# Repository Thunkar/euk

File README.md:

# EUK Split Keyboard

A split ergonomic keyboard project with customizable accessories and per-key RGB lighting.

## Features

- Split design for ergonomic typing
- Hot-swappable MX switches
- Per-key RGB lighting (SK6812 mini-e LEDs)
- RP2040-based controller
- Optional accessories:
  - OLED screen
  - Rotary encoder
  - Analog joystick
  - Potentiometer
  - Tenting support

## Documentation

- [Bill of Materials (BOM)](./split/docs/BOM.md) - Complete list of components needed
- [Ordering PCBs](./split/docs/ORDERING_PCBS.md) - Guide for ordering the printed circuit boards
- [Assembly Guide](./split/docs/ASSEMBLY.md) - Step-by-step assembly instructions

## Project Structure

- `cad/` - 3D printable case and accessory files
- `pcb/` - KiCad PCB design files
- `docs/` - Documentation and guides
- `via.layout.json` - VIA keyboard configurator layout
- `via.definition.json` - VIA keyboard definition
- `kle.definition.json` - https://keyboard-layout-editor.com/ definition

## Getting Started

1. Review the [BOM](docs/BOM.md) to buy all required components
2. Follow the [PCB ordering guide](docs/ORDERING_PCBS.md) and get yourself some boards
3. Print the required parts from the `cad/` directory
4. Follow the [assembly guide](docs/ASSEMBLY.md) to build it!

## Firmware

This keyboard uses QMK/VIA firmware. Use the included `via.layout.json` file to configure your keyboard layout in [VIA](https://usevia.app/).

At the moment, use the QMK fork at https://github.com/Thunkar/qmk_firmware

After installation, flash with:

`qmk flash -kb euk/split -km default`

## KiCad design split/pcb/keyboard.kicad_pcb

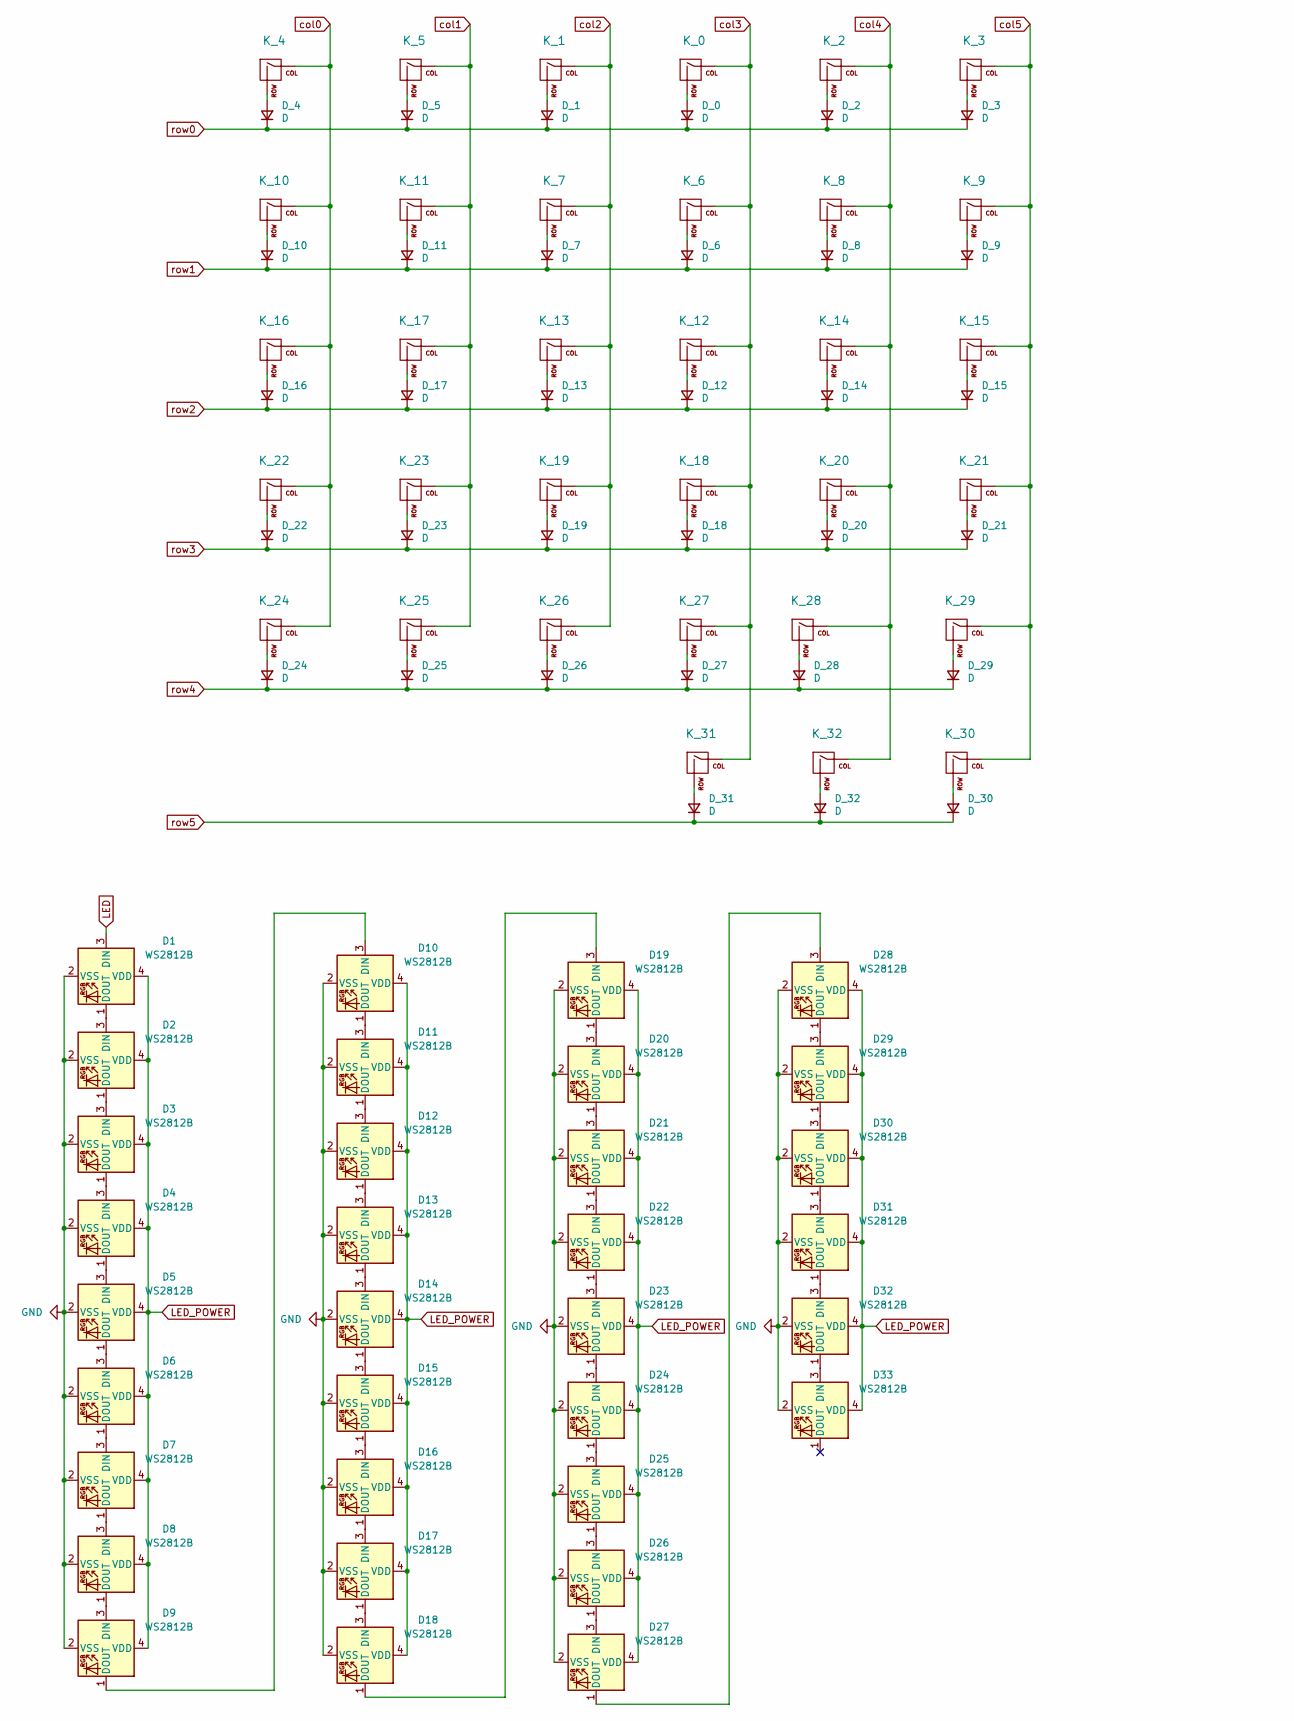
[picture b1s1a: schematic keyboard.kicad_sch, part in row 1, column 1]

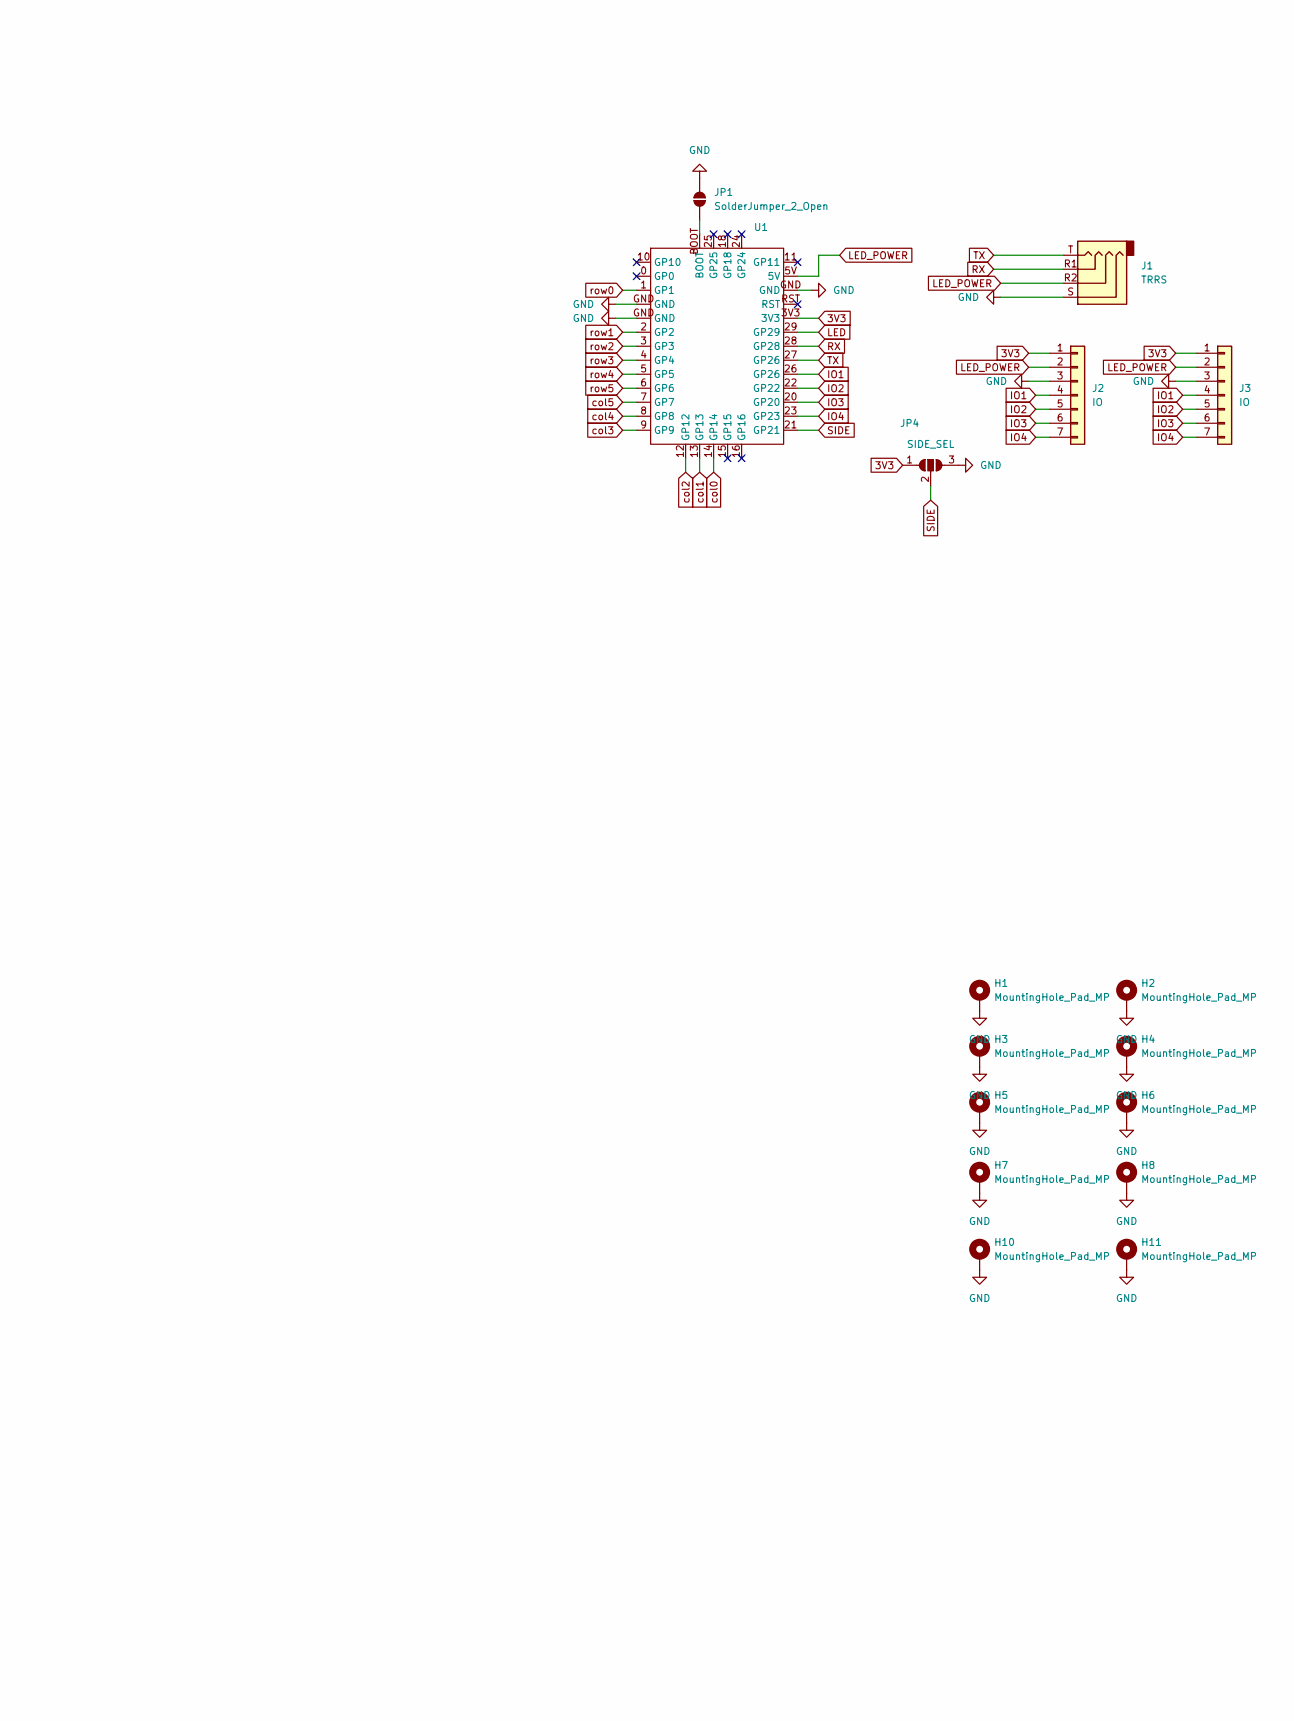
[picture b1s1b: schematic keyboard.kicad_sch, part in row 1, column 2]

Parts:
D1, D2, D3, D4, D5, D6, D7, D8, D9, D10, D11, D12, D13, D14, D15, D16, D17, D18, D19, D20, D21, D22, D23, D24, D25, D26, D27, D28, D29, D30, D31, D32, D33: WS2812B; SK6812-MINI-E
D_0, D_1, D_2, D_3, D_4, D_5, D_6, D_7, D_8, D_9, D_10, D_11, D_12, D_13, D_14, D_15, D_16, D_17, D_18, D_19, D_20, D_21, D_22, D_23, D_24, D_25, D_26, D_27, D_28, D_29, D_30, D_31, D_32: D; D_SOD-123_Reversible
H1, H2, H3, H4, H5, H6, H7, H8, H10, H11: MountingHole_Pad_MP; MountingHole_2.2mm_M2_DIN965_Pad
J1: TRRS; TRRS_JACK_MJ4PP9
J2, J3: IO; PinHeader_1x07_P2.54mm_Vertical
JP1: SolderJumper_2_Open; SolderJumper-2_P1.3mm_Open_Pad1.0x1.5mm
JP4: SIDE_SEL; SolderJumper-3_P1.3mm_Open_Pad1.0x1.5mm
K_0, K_1, K_2, K_3, K_4, K_5, K_6, K_7, K_8, K_9, K_10, K_11, K_12, K_13, K_14, K_15, K_16, K_17, K_18, K_19, K_20, K_21, K_22, K_23, K_24, K_25, K_26, K_27, K_28, K_29, K_30, K_31, K_32: KEYSW; Kailh_socket_MX_reversible
U1: pro_micro_rp2040

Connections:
3V3: J2.1, J3.1, JP4.1 (A), U1.3V3
GND: D1.2 (VSS), D2.2 (VSS), D3.2 (VSS), D4.2 (VSS), D5.2 (VSS), D6.2 (VSS), D7.2 (VSS), D8.2 (VSS), D9.2 (VSS), D10.2 (VSS), D11.2 (VSS), D12.2 (VSS), D13.2 (VSS), D14.2 (VSS), D15.2 (VSS), D16.2 (VSS), D17.2 (VSS), D18.2 (VSS), D19.2 (VSS), D20.2 (VSS), D21.2 (VSS), D22.2 (VSS), D23.2 (VSS), D24.2 (VSS), D25.2 (VSS), D26.2 (VSS), D27.2 (VSS), D28.2 (VSS), D29.2 (VSS), D30.2 (VSS), D31.2 (VSS), D32.2 (VSS), D33.2 (VSS), H1.1, H2.1, H3.1, H4.1, H5.1, H6.1, H7.1, H8.1, H10.1, H11.1, J1.S, J2.3, J3.3, JP1.2 (B), JP4.3 (B), U1.GND
IO1: J2.4, J3.4, U1.26 (GP26)
IO2: J2.5, J3.5, U1.22 (GP22)
IO3: J2.6, J3.6, U1.20 (GP20)
IO4: J2.7, J3.7, U1.23 (GP23)
LED: D1.3 (DIN), U1.29 (GP29)
LED_POWER: D1.4 (VDD), D2.4 (VDD), D3.4 (VDD), D4.4 (VDD), D5.4 (VDD), D6.4 (VDD), D7.4 (VDD), D8.4 (VDD), D9.4 (VDD), D10.4 (VDD), D11.4 (VDD), D12.4 (VDD), D13.4 (VDD), D14.4 (VDD), D15.4 (VDD), D16.4 (VDD), D17.4 (VDD), D18.4 (VDD), D19.4 (VDD), D20.4 (VDD), D21.4 (VDD), D22.4 (VDD), D23.4 (VDD), D24.4 (VDD), D25.4 (VDD), D26.4 (VDD), D27.4 (VDD), D28.4 (VDD), D29.4 (VDD), D30.4 (VDD), D31.4 (VDD), D32.4 (VDD), D33.4 (VDD), J1.R2, J2.2, J3.2, U1.5V
unnamed: D1.1 (DOUT), D2.3 (DIN)
unnamed: D2.1 (DOUT), D3.3 (DIN)
unnamed: D3.1 (DOUT), D4.3 (DIN)
unnamed: D4.1 (DOUT), D5.3 (DIN)
unnamed: D5.1 (DOUT), D6.3 (DIN)
unnamed: D6.1 (DOUT), D7.3 (DIN)
unnamed: D7.1 (DOUT), D8.3 (DIN)
unnamed: D8.1 (DOUT), D9.3 (DIN)
unnamed: D9.1 (DOUT), D10.3 (DIN)
unnamed: D10.1 (DOUT), D11.3 (DIN)
unnamed: D11.1 (DOUT), D12.3 (DIN)
unnamed: D12.1 (DOUT), D13.3 (DIN)
unnamed: D13.1 (DOUT), D14.3 (DIN)
unnamed: D14.1 (DOUT), D15.3 (DIN)
unnamed: D15.1 (DOUT), D16.3 (DIN)
unnamed: D16.1 (DOUT), D17.3 (DIN)
unnamed: D17.1 (DOUT), D18.3 (DIN)
unnamed: D18.1 (DOUT), D19.3 (DIN)
unnamed: D19.1 (DOUT), D20.3 (DIN)
unnamed: D20.1 (DOUT), D21.3 (DIN)
unnamed: D21.1 (DOUT), D22.3 (DIN)
unnamed: D22.1 (DOUT), D23.3 (DIN)
unnamed: D23.1 (DOUT), D24.3 (DIN)
unnamed: D24.1 (DOUT), D25.3 (DIN)
unnamed: D25.1 (DOUT), D26.3 (DIN)
unnamed: D26.1 (DOUT), D27.3 (DIN)
unnamed: D27.1 (DOUT), D28.3 (DIN)
unnamed: D28.1 (DOUT), D29.3 (DIN)
unnamed: D29.1 (DOUT), D30.3 (DIN)
unnamed: D30.1 (DOUT), D31.3 (DIN)
unnamed: D31.1 (DOUT), D32.3 (DIN)
unnamed: D32.1 (DOUT), D33.3 (DIN)
unnamed: D_0.2 (A), K_0.2 (ROW)
unnamed: D_1.2 (A), K_1.2 (ROW)
unnamed: D_2.2 (A), K_2.2 (ROW)
unnamed: D_3.2 (A), K_3.2 (ROW)
unnamed: D_4.2 (A), K_4.2 (ROW)
unnamed: D_5.2 (A), K_5.2 (ROW)
unnamed: D_6.2 (A), K_6.2 (ROW)
unnamed: D_7.2 (A), K_7.2 (ROW)
unnamed: D_8.2 (A), K_8.2 (ROW)
unnamed: D_9.2 (A), K_9.2 (ROW)
unnamed: D_10.2 (A), K_10.2 (ROW)
unnamed: D_11.2 (A), K_11.2 (ROW)
unnamed: D_12.2 (A), K_12.2 (ROW)
unnamed: D_13.2 (A), K_13.2 (ROW)
unnamed: D_14.2 (A), K_14.2 (ROW)
unnamed: D_15.2 (A), K_15.2 (ROW)
unnamed: D_16.2 (A), K_16.2 (ROW)
unnamed: D_17.2 (A), K_17.2 (ROW)
unnamed: D_18.2 (A), K_18.2 (ROW)
unnamed: D_19.2 (A), K_19.2 (ROW)
unnamed: D_20.2 (A), K_20.2 (ROW)
unnamed: D_21.2 (A), K_21.2 (ROW)
unnamed: D_22.2 (A), K_22.2 (ROW)
unnamed: D_23.2 (A), K_23.2 (ROW)
unnamed: D_24.2 (A), K_24.2 (ROW)
unnamed: D_25.2 (A), K_25.2 (ROW)
unnamed: D_26.2 (A), K_26.2 (ROW)
unnamed: D_27.2 (A), K_27.2 (ROW)
unnamed: D_28.2 (A), K_28.2 (ROW)
unnamed: D_29.2 (A), K_29.2 (ROW)
unnamed: D_30.2 (A), K_30.2 (ROW)
unnamed: D_31.2 (A), K_31.2 (ROW)
unnamed: D_32.2 (A), K_32.2 (ROW)
unnamed: JP1.1 (A), U1.BOOT
RX: J1.R1, U1.28 (GP28)
SIDE: JP4.2 (C), U1.21 (GP21)
TX: J1.T, U1.27 (GP26)
col0: K_4.1 (COL), K_10.1 (COL), K_16.1 (COL), K_22.1 (COL), K_24.1 (COL), U1.14 (GP14)
col1: K_5.1 (COL), K_11.1 (COL), K_17.1 (COL), K_23.1 (COL), K_25.1 (COL), U1.13 (GP13)
col2: K_1.1 (COL), K_7.1 (COL), K_13.1 (COL), K_19.1 (COL), K_26.1 (COL), U1.12 (GP12)
col3: K_0.1 (COL), K_6.1 (COL), K_12.1 (COL), K_18.1 (COL), K_27.1 (COL), K_31.1 (COL), U1.9 (GP9)
col4: K_2.1 (COL), K_8.1 (COL), K_14.1 (COL), K_20.1 (COL), K_28.1 (COL), K_32.1 (COL), U1.8 (GP8)
col5: K_3.1 (COL), K_9.1 (COL), K_15.1 (COL), K_21.1 (COL), K_29.1 (COL), K_30.1 (COL), U1.7 (GP7)
row0: D_0.1 (K), D_1.1 (K), D_2.1 (K), D_3.1 (K), D_4.1 (K), D_5.1 (K), U1.1 (GP1)
row1: D_6.1 (K), D_7.1 (K), D_8.1 (K), D_9.1 (K), D_10.1 (K), D_11.1 (K), U1.2 (GP2)
row2: D_12.1 (K), D_13.1 (K), D_14.1 (K), D_15.1 (K), D_16.1 (K), D_17.1 (K), U1.3 (GP3)
row3: D_18.1 (K), D_19.1 (K), D_20.1 (K), D_21.1 (K), D_22.1 (K), D_23.1 (K), U1.4 (GP4)
row4: D_24.1 (K), D_25.1 (K), D_26.1 (K), D_27.1 (K), D_28.1 (K), D_29.1 (K), U1.5 (GP5)
row5: D_30.1 (K), D_31.1 (K), D_32.1 (K), U1.6 (GP6)

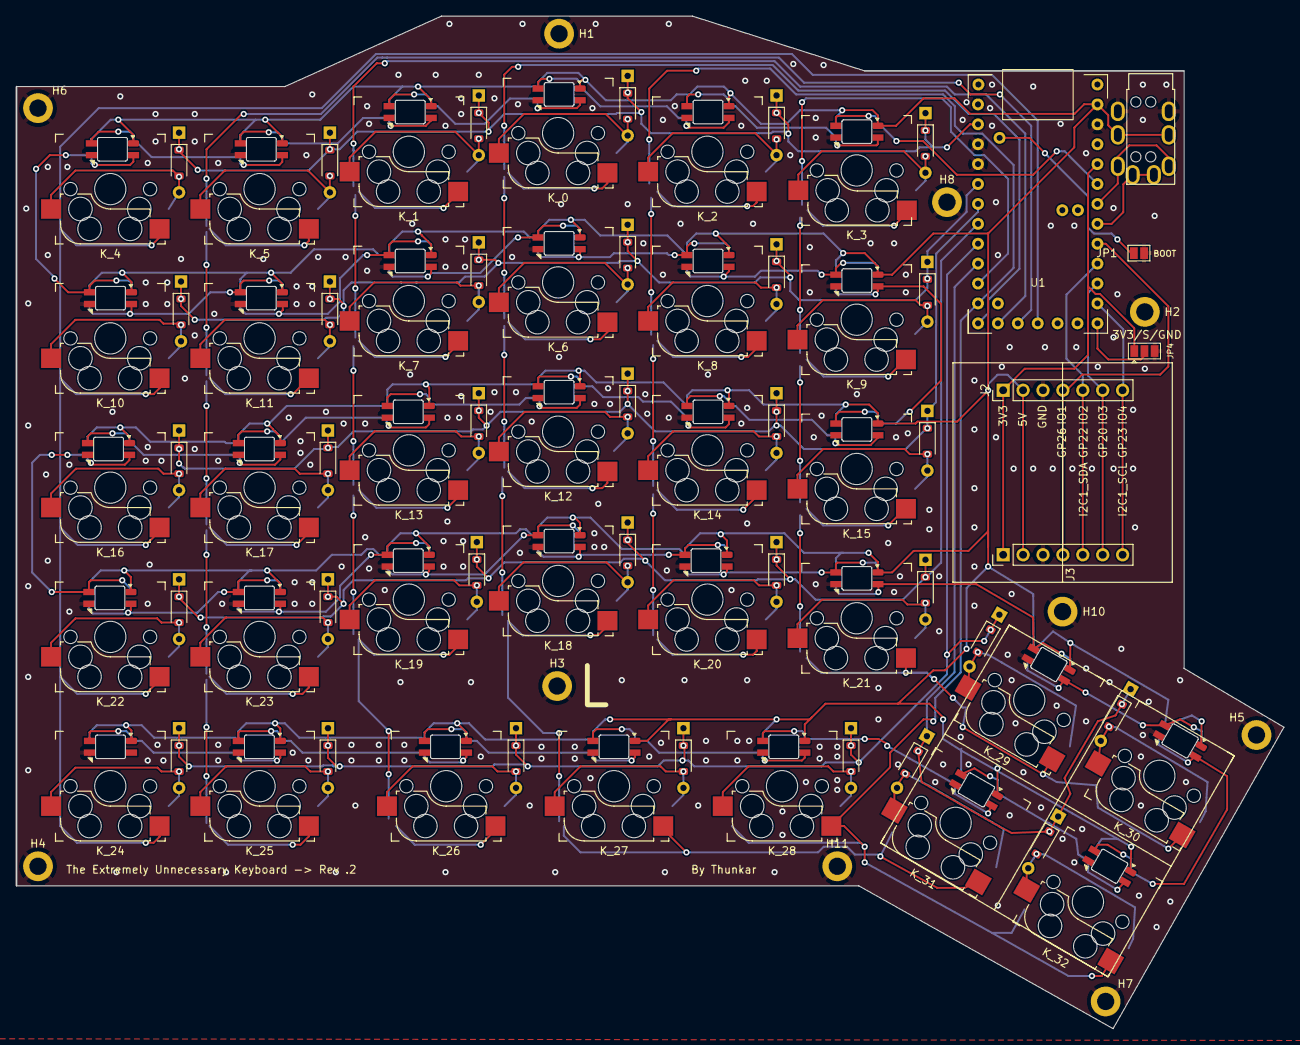
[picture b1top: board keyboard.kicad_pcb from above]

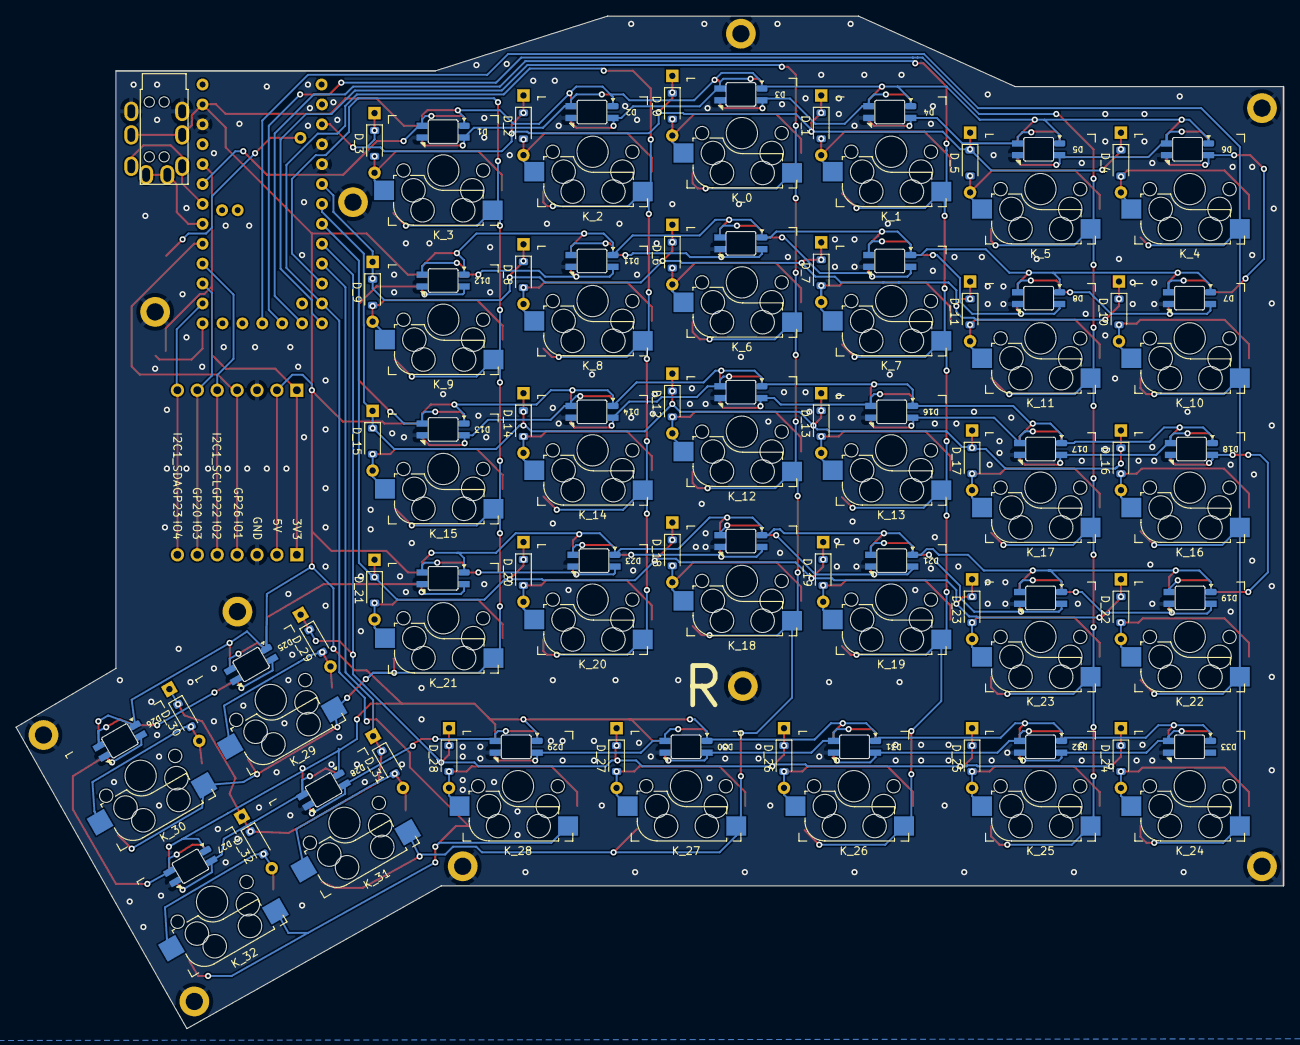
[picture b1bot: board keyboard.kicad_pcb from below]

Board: 2 copper layers, 161.7 x 129.1 mm, 115 parts (98 on the bottom side), 89 nets.

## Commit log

2025-08-01 initial
2025-08-01 mini
2025-08-05 reorg
2025-08-05 fixes
2025-08-06 led_calc
2025-08-10 fix accessory connector
2025-08-11 complete layout and via file
2025-08-16 pcb fixes
2025-08-17 fixed via file
2025-08-19 layout started
2025-08-19 new attempt
2025-08-20 more keys
2025-08-20 working layout
2025-08-21 closer thumbcluster, more layout
2025-08-22 more layout
2025-08-22 pcb tweaks
2025-09-14 missing changes
2025-09-29 added boot hole
2025-10-04 stls
2025-10-11 layout
2025-10-27 docs
2025-10-27 tweaks
2026-02-09 fix bom and layout
